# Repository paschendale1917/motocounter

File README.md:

###	Счетчик моточасов с системой меню и управлением с помощью трехпозиционного слайдера

- **Микроконтроллер:** STM32G030F6P6 
- **Частота:** 64 МГц
- **IDE:** Keil uVision
- **Compiler:** v6.19
- **Язык:** C (Embedded)
- **Дисплей:** LCD ST7735 0.96" 80_160(IPS), 1.8" 128_160(TN), 0.85" 128_128(IPS)
- **Задействованная периферия:** таймеры, АЦП, SPI, I2C, DMA
- **Управление:** Трехпозиционная кнопка(слайдер)
- **Программатор:** ST-Link v2

###	Больше по дисплею
- можно любой на драйвере ST7735, но в дефайнах изменить разрешение, а также параметры LCD_HEIGHT_OFFSET и LCD_WIDTH_OFFSET выставить на 0, либо подобрать свои смещения
- возможно придется поиграться с регистрами MADCTL и INVON/INVOFF дисплея для установки верной ориентации и режима отображения цветов

###	Больше по периферии
- Нажатия слайдера обрабатываются в прерываниях таймера TIM1. Распознаются длительные и короткие нажатия
- Подсветка дисплея использует таймер TIM14  в режиме ШИМ
- Баззер использует таймер TIM17 в режиме ШИМ
- Счетчик организован на таймере TIM16
- Светодиоды WS2812 используют таймер TIM3 и канал 1 DMA1
- Вольтметр использует канал 10 мультиплексора АЦП и канал 2 DMA1
- Дисплей на SPI1
- EEPROM на I2C2
- WWDG

###	Клонирование репозитория
git clone https://github.com/paschendale1917/motocounter.git

###	Принцип работы:
После подачи питания устройство считывает из EEPROM настроечные константы, измеряет напряжение в бортовой сети и отображает на главном экране
 количество наработанных моточасов,напряжение бортовой сети и уставку моточасов, при достижении значения которой счетчик будет подавать светозвуковой сигнал.
При заведенном двигателе напряжение в бортовой сети повышается и при достижении порогового значения начинается отсчет времени.
Из меню можно настроить:
- величину порогового значения напряжения в бортовой сети для старта отсчета времени наработки
- уставку моточасов для подачи светозвуковой сигнализации при превышении счетчиком ее значения
- величину значения делителя(для того, чтобы не разбирать корпус и не подстраивать потенциометр на входе АЦП)
- цвет индикации превышения значения счетчика уставки моточасов
- яркость подсветки дисплея

При снижении напряжения питания ниже порогового значения прекращается отсчет времени и производится запись значения счетчика в EEPROM.
Все остальные настраиваемые константы также сохраняются в EEPROM.
Для того, чтобы при резком отключении питания была возможность сохранения всех настроек и значения счетчика, на входе по питанию установлены 2 конденсатора по 1000 мкФ. 
Через минуту после последней активности органов управления подсветка дисплея снижается до минимума.
 
###	Управление:
- вход в меню из главного экрана по длительному нажатию на центр слайдера
- выход из меню на скринсейвер по длительному отклонению слайдера влево
- вход в дочернее меню (child) по короткому нажатию на центр слайдера
- выход в родительское меню (parent) по длительному отклонению слайдера влево
- вход в обработчик пункта меню по короткому нажатию на центр слайдера
- выход из обработчика пункта меню по длительному отклонению слайдера влево
- согласие на системный ресет или сброс счетчика моточасов по длительному отклонению слайдера вправо

###	Краткое описание системы меню:
- Создана структура, в которой описаны связи пунктов меню(двунаправленные связные списки)между друг другом и обработчиками состояния меню(КА).
- В бесконечном цикле мониторится состояние переменной menustate(состояние меню),состояние флагов органов управления, отслеживаются изменения в состоянии меню,которое перерисовывается в соответствии с этими изменениями. 
	Также здесь работает функция display_pointer(pointer), которая меняет положение указателя в соответствии с активным пунктом меню(всегда указывает на него). Координаты указателя явно заданы в структуре. 
	Всё это происходит до того момента, пока переменная menustate не примет значение, соответствующее номеру одного из обработчиков.
- Как только зафиксировано изменение в состоянии органов управления(нажатие кнопки или вращение вала энкодера), то происходит действие в соответствии с заданным функционалом в process_menu() и связями, установленными 
	в структуре пункта меню-это либо вход в обработчик, либо в дочернее меню, либо перемещение по меню.
- При входе в обработчик в переменную menustate записывается его номер и таким образом process_menu() передает ему управление. Далее программа действует в соответствии с внутренней логикой обработчика.
- При выходе из обработчика в переменную menustate записывается значение, не соответствующее ни одному из номеров обработчиков, что возвращает управление функции process_menu().
- При старте в переменной menustate записан 0, что соответствует обработчику скринсейвера.
 
###	Внимание!
- Уверенно измеряет напряжение от 7 до 22 вольт, чтобы изменить диапазон, требуется подобрать иную элементную базу
- Нужно помнить, что чем выше входное напряжение, тем выше нагрев(78M05), поэтому беспроблемная эксплуатация возможна только на легковом 
 автомобиле с номинальным напряжением бортовой сети 12 в

###	TO DO:
- ...

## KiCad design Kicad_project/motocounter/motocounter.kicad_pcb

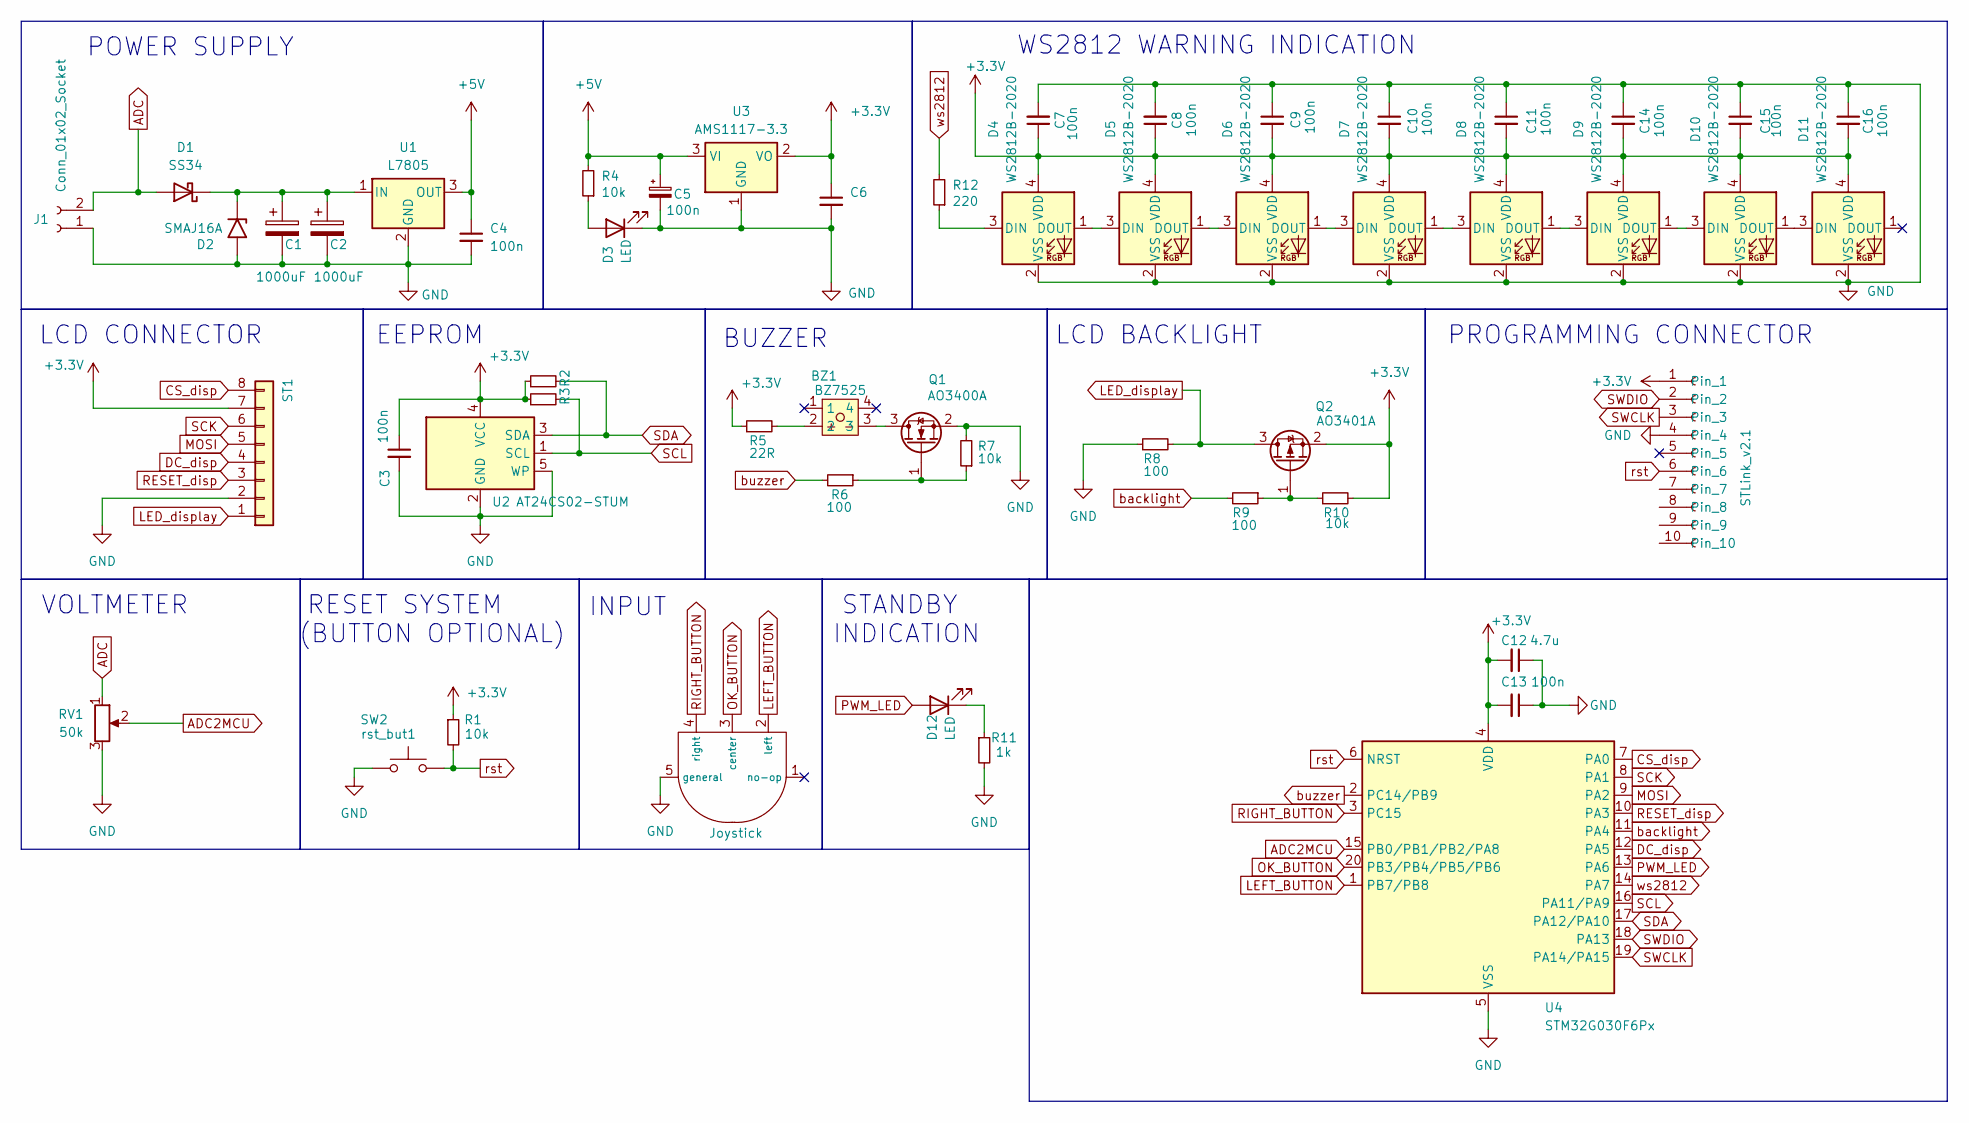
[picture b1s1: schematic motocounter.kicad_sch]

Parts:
BZ1: BZ7525; Buzzer_7525
C1, C2: 1000uF; CP_Radial_D10.0mm_P5.00mm
C3, C4, C13: 100n; C_0805_2012Metric_Pad1.18x1.45mm_HandSolder
C5: 100n; C_1210_3225Metric
C6: 2.2uF; C_0805_2012Metric_Pad1.18x1.45mm_HandSolder
C7, C8, C9, C10, C11, C14, C15, C16: 100n; C_0603_1608Metric
C12: 4.7u; C_0805_2012Metric_Pad1.18x1.45mm_HandSolder
D1: SS34; D_SMA
D2: SMAJ16A; D_SMB
D3: LED; LED_0805_2012Metric_Pad1.15x1.40mm_HandSolder
D4, D5, D6, D7, D8, D9, D10, D11: WS2812B-2020; LED_WS2812B-2020_PLCC4_2.0x2.0mm
D12: LED; LED_0603_1608Metric
J1: Conn_01x02_Socket; JST_XH_B2B-XH-A_1x02_P2.50mm_Vertical
Joystick: slide_button
Q1: AO3400A; SOT-23
Q2: AO3401A; SOT-23
R1, R2, R3, R4, R7, R10: 10k; R_0805_2012Metric_Pad1.20x1.40mm_HandSolder
R5: 22R; R_0805_2012Metric_Pad1.20x1.40mm_HandSolder
R6, R8, R9: 100; R_0805_2012Metric_Pad1.20x1.40mm_HandSolder
R11: 1k; R_0603_1608Metric
R12: 220; R_0805_2012Metric_Pad1.20x1.40mm_HandSolder
RV1: 50k; Potentiometer_Runtron_RM-065_Vertical
ST1: display; Hirose_FH12-8S-0.5SH_1x08-1MP_P0.50mm_Horizontal
STLink_v2.1: JST_SH_SM10B-SRSS-TB_1x10-1MP_P1.00mm_Horizontal
U1: L7805; TO-252-2
U2: AT24CS02-STUM; SOT-23-5_HandSoldering
U3: AMS1117-3.3; SOT-223-3_TabPin2
U4: STM32G030F6Px; TSSOP-20_4.4x6.5mm_P0.65mm
rst_but1: SW2; SW_SPST_PTS810

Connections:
+3.3V: C3.1, C6.1, C7.1, C8.1, C9.2, C10.2, C11.2, C12.2, C13.2, C14.2, C15.2, C16.2, D4.4 (VDD), D5.4 (VDD), D6.4 (VDD), D7.4 (VDD), D8.4 (VDD), D9.4 (VDD), D10.4 (VDD), D11.4 (VDD), Q2.2 (S), R1.1, R2.1, R3.1, R5.1, R10.2, ST1.7, STLink_v2.1.1, U2.4 (VCC), U3.2 (VO), U4.4 (VDD)
+5V: C4.1, C5.1, R4.2, U1.3 (OUT), U3.3 (VI)
ADC: D1.2 (A), J1.2, RV1.1
ADC2MCU: RV1.2, U4.15 (PB0/PB1/PB2/PA8)
CS_disp: ST1.8, U4.7 (PA0)
DC_disp: ST1.4, U4.12 (PA5)
GND: C1.2, C2.2, C3.2, C4.2, C5.2, C6.2, C7.2, C8.2, C9.1, C10.1, C11.1, C12.1, C13.1, C14.1, C15.1, C16.1, D2.2 (A2), D3.1 (K), D4.2 (VSS), D5.2 (VSS), D6.2 (VSS), D7.2 (VSS), D8.2 (VSS), D9.2 (VSS), D10.2 (VSS), D11.2 (VSS), J1.1, Joystick.5 (general), Q1.2 (S), R7.2, R8.1, R11.2, RV1.3, ST1.2, STLink_v2.1.4, U1.2 (GND), U2.2 (GND), U2.5 (WP), U3.1 (GND), U4.5 (VSS), rst_but1.1
LED_display: Q2.3 (D), R8.2, ST1.1
LEFT_BUTTON: Joystick.2 (left), U4.1 (PB7/PB8)
MOSI: ST1.5, U4.9 (PA2)
unnamed: BZ1.2, R5.2
unnamed: C1.1, C2.1, D1.1 (K), D2.1 (A1), U1.1 (IN)
unnamed: D3.2 (A), R4.1
unnamed: D4.3 (DIN), R12.1
unnamed: D4.1 (DOUT), D5.3 (DIN)
unnamed: D5.1 (DOUT), D6.3 (DIN)
unnamed: D6.1 (DOUT), D7.3 (DIN)
unnamed: D7.1 (DOUT), D8.3 (DIN)
unnamed: D8.1 (DOUT), D9.3 (DIN)
unnamed: D9.1 (DOUT), D10.3 (DIN)
unnamed: D10.1 (DOUT), D11.3 (DIN)
unnamed: D12.1 (K), R11.1
unnamed: BZ1.3, Q1.3 (D)
unnamed: Q1.1 (G), R6.1, R7.1
unnamed: Q2.1 (G), R9.1, R10.1
OK_BUTTON: Joystick.3 (center), U4.20 (PB3/PB4/PB5/PB6)
PWM_LED: D12.2 (A), U4.13 (PA6)
RESET_disp: ST1.3, U4.10 (PA3)
RIGHT_BUTTON: Joystick.4 (right), U4.3 (PC15)
SCK: ST1.6, U4.8 (PA1)
SCL: R3.2, U2.1 (SCL), U4.16 (PA11/PA9)
SDA: R2.2, U2.3 (SDA), U4.17 (PA12/PA10)
SWCLK: STLink_v2.1.3, U4.19 (PA14/PA15)
SWDIO: STLink_v2.1.2, U4.18 (PA13)
backlight: R9.2, U4.11 (PA4)
buzzer: R6.2, U4.2 (PC14/PB9)
rst: R1.2, STLink_v2.1.6, U4.6 (NRST), rst_but1.2
ws2812: R12.2, U4.14 (PA7)

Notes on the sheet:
EEPROM
PROGRAMMING CONNECTOR
POWER SUPPLY
LCD BACKLIGHT
VOLTMETER
WS2812 WARNING INDICATION
RESET SYSTEM (BUTTON OPTIONAL)
INPUT
BUZZER
STANDBY INDICATION
LCD CONNECTOR

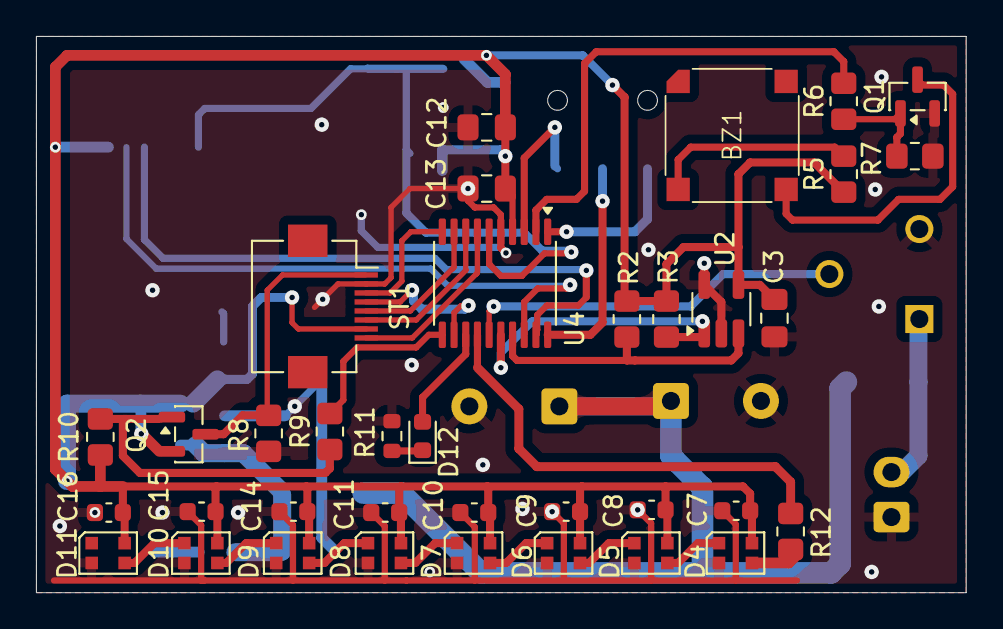
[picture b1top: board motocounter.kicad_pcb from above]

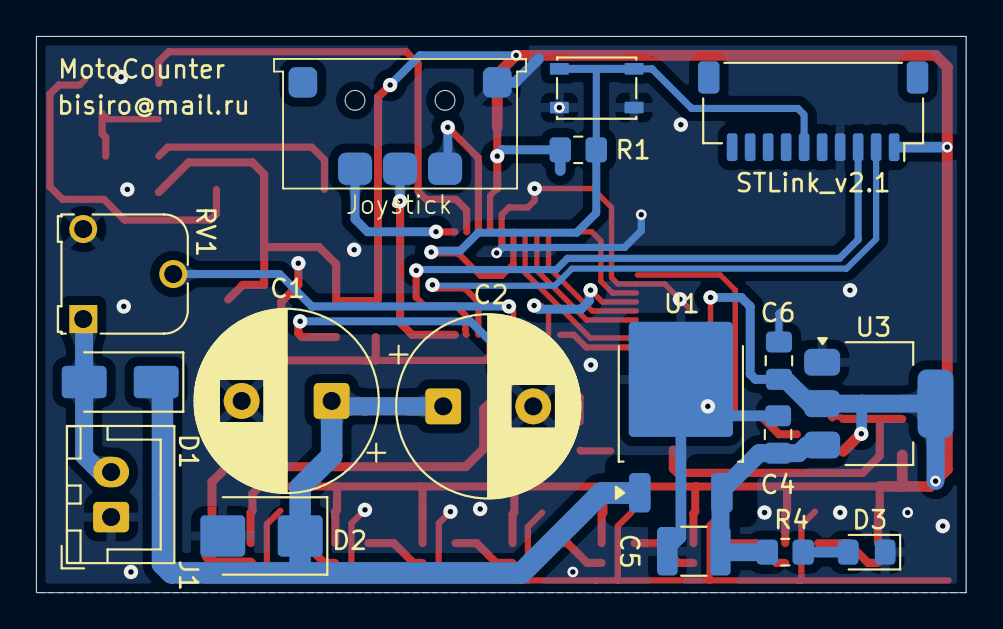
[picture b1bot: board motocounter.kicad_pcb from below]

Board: 2 copper layers, 51.6 x 30.9 mm, 53 parts (17 on the bottom side), 38 nets.

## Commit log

2025-11-21 update 21/11
2025-11-24 update 24/11
2025-11-25 update 25/11
2025-11-26 update 26/11
2025-11-29 update 30/11
2025-12-12 update 12/11
2025-12-12 update 12/12
